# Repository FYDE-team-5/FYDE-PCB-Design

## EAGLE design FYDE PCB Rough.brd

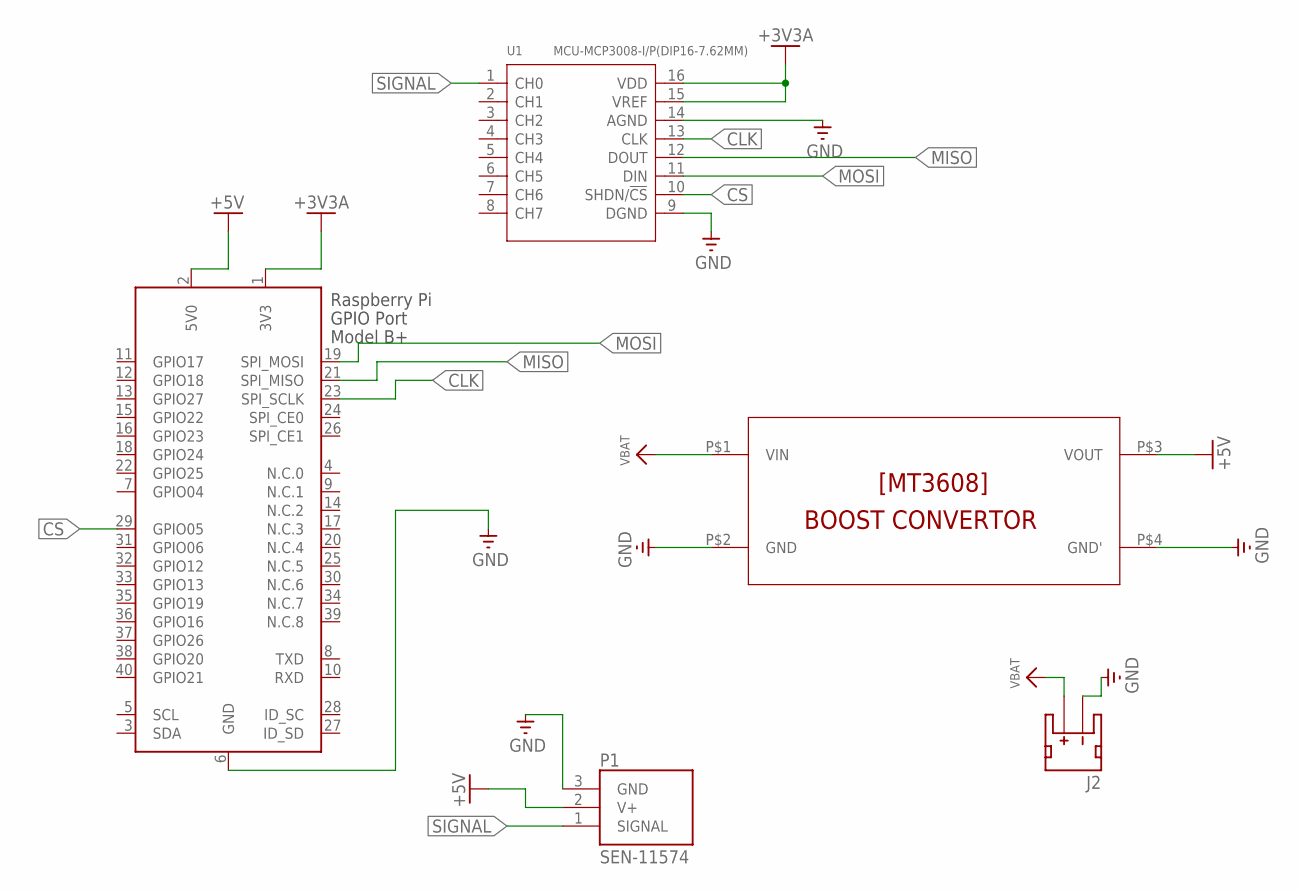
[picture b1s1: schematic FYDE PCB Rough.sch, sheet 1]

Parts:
J2: JST_2MM_MALE; JST-2-SMD
P1: SEN-11574; XDCR_SEN-11574
U1: MCU-MCP3008-I/P(DIP16-7.62MM); DIP16-2.54-19.2X7.62MM
U$2: MT3608
X1: RASPI_BOARD_B+_HDC; RASPI_BOARD_B+HAT_DF_CF

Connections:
+3V3A: U1.15 (VREF), U1.16 (VDD), X1.1 (3V3)
+5V: P1.2 (V+), U$2.P$3 (VOUT), X1.2 (5V0)
CLK: U1.13 (CLK), X1.23 (SPI_SCLK)
CS: U1.10 (SHDN/!CS), X1.29 (GPIO05)
GND: J2.1 (-), P1.3 (GND), U1.9 (DGND), U1.14 (AGND), U$2.P$2 (GND), U$2.P$4 (GND'), X1.6 (GND)
MISO: U1.12 (DOUT), X1.21 (SPI_MISO)
MOSI: U1.11 (DIN), X1.19 (SPI_MOSI)
SIGNAL: P1.1 (SIGNAL), U1.1 (CH0)
VBAT: J2.2 (+), U$2.P$1 (VIN)

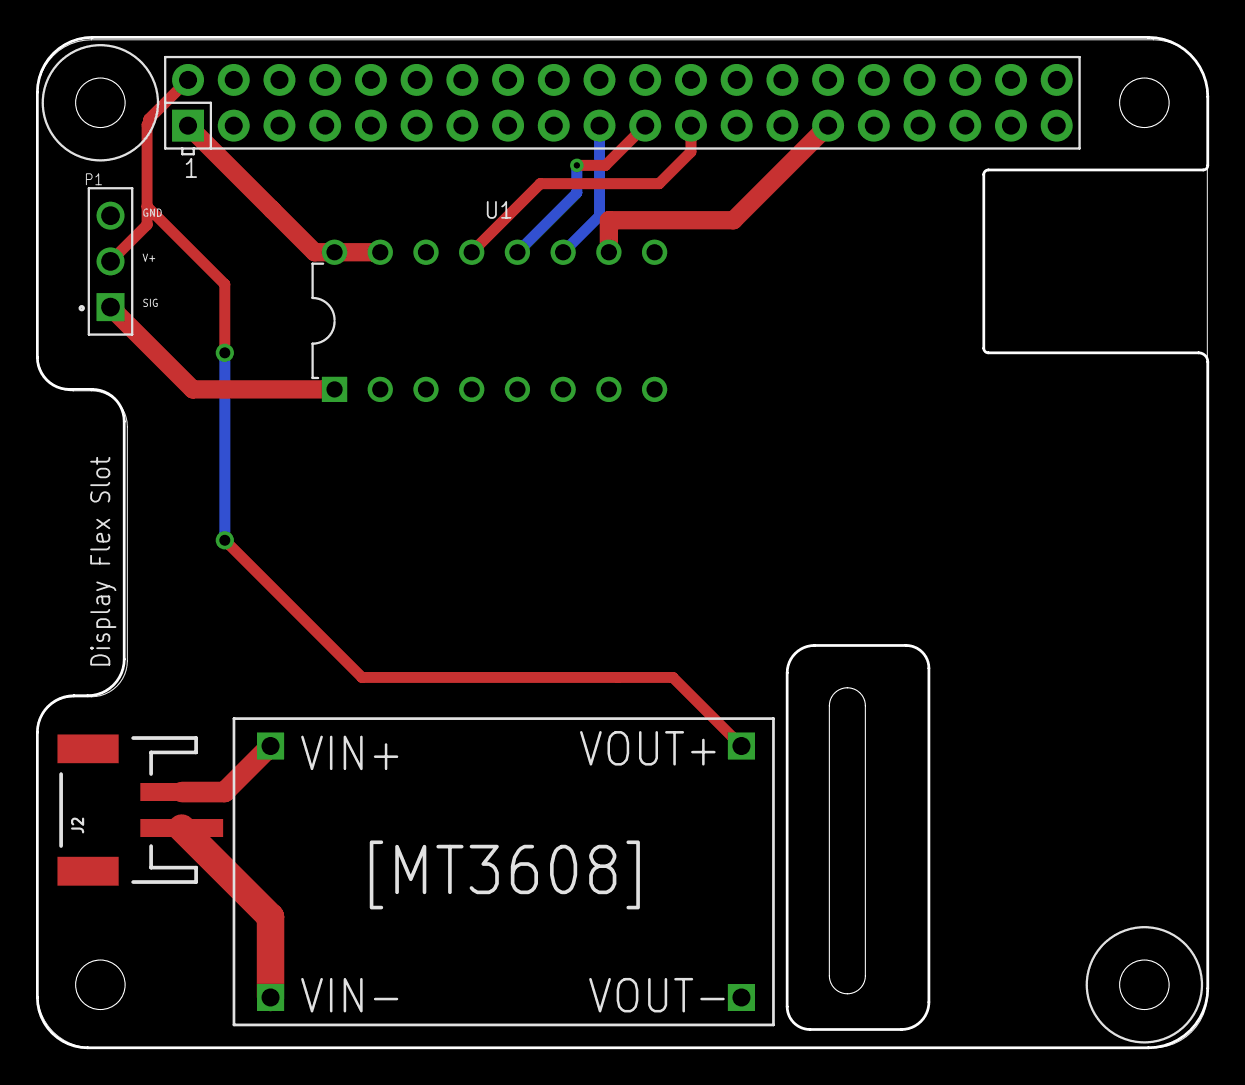
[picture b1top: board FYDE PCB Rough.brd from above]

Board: 2 copper layers, 65.0 x 56.1 mm, 5 parts (0 on the bottom side), 9 nets.

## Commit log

2020-04-10 hear rate headphones schematic
2020-04-14 Add files via upload
    added parts into schematic / board design
2020-04-14 Add files via upload
    updated, more concise
2020-04-15 updated; includes Power Booster custom library
2020-04-17 ADC converter
2020-04-20 schematic missing extra holes
2020-04-20 Add files via upload
    now with holes!
2020-04-21 Add files via upload
    new powerbooster (with library)
2020-04-24 zip file for submission Prelim PCB

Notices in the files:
parts and their libraries:
SparkFun-Connectors: Licensing: Creative Commons ShareAlike 4.0 International - https://creativecommons.org/licenses/by-sa/4.0
supply0: Copyright (C) 2007, Bob Starr
